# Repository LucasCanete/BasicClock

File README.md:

# BasicClock
Small atmega328p-based Clock displays the time, the temperature and humidity of the room.

## Table of Contents
1. [About the Project](#about-the-project)
2. [Project Status](#project-status)
3. [Getting Started](#getting-started)

## About the Project
Every Christmas I have to think hard what to give as a gift to my friends. As the Maker i am i decided to develop a device i could always give as a gift in Birthdays or Christmas when i dont come with any better idea. The device is a simple Clock with a big display and three buttons. The Clock lets the user see the time, temperature and humidity of the room. Additionally, the user can configure the time in case time changes or the person moves to a different timezone.

Besides from all this, i just wanted to try program different sensors with the Atmega328p using C++. I found it very convenient with the OOP so i might keep using it in the future.

Features:
- Visualization of current date, hour, temperature and humidity
- Configuration of date and hour
- USB-C port for UART communication
- Small design for being portable

## Project Status
Project is currently under development. Next Steps are the following:
- [x] Order Board from JLCPCB
- [ ] Order Stencil (i forgot it the first time)
- [ ] Solder SMD Components
- [ ] Test BME280
- [ ] Test RTC
- [ ] Test USB-C UART Communication
- [ ] Write driver for Display
- [ ] Finish writing the firmware

## Getting Started
Coming soon

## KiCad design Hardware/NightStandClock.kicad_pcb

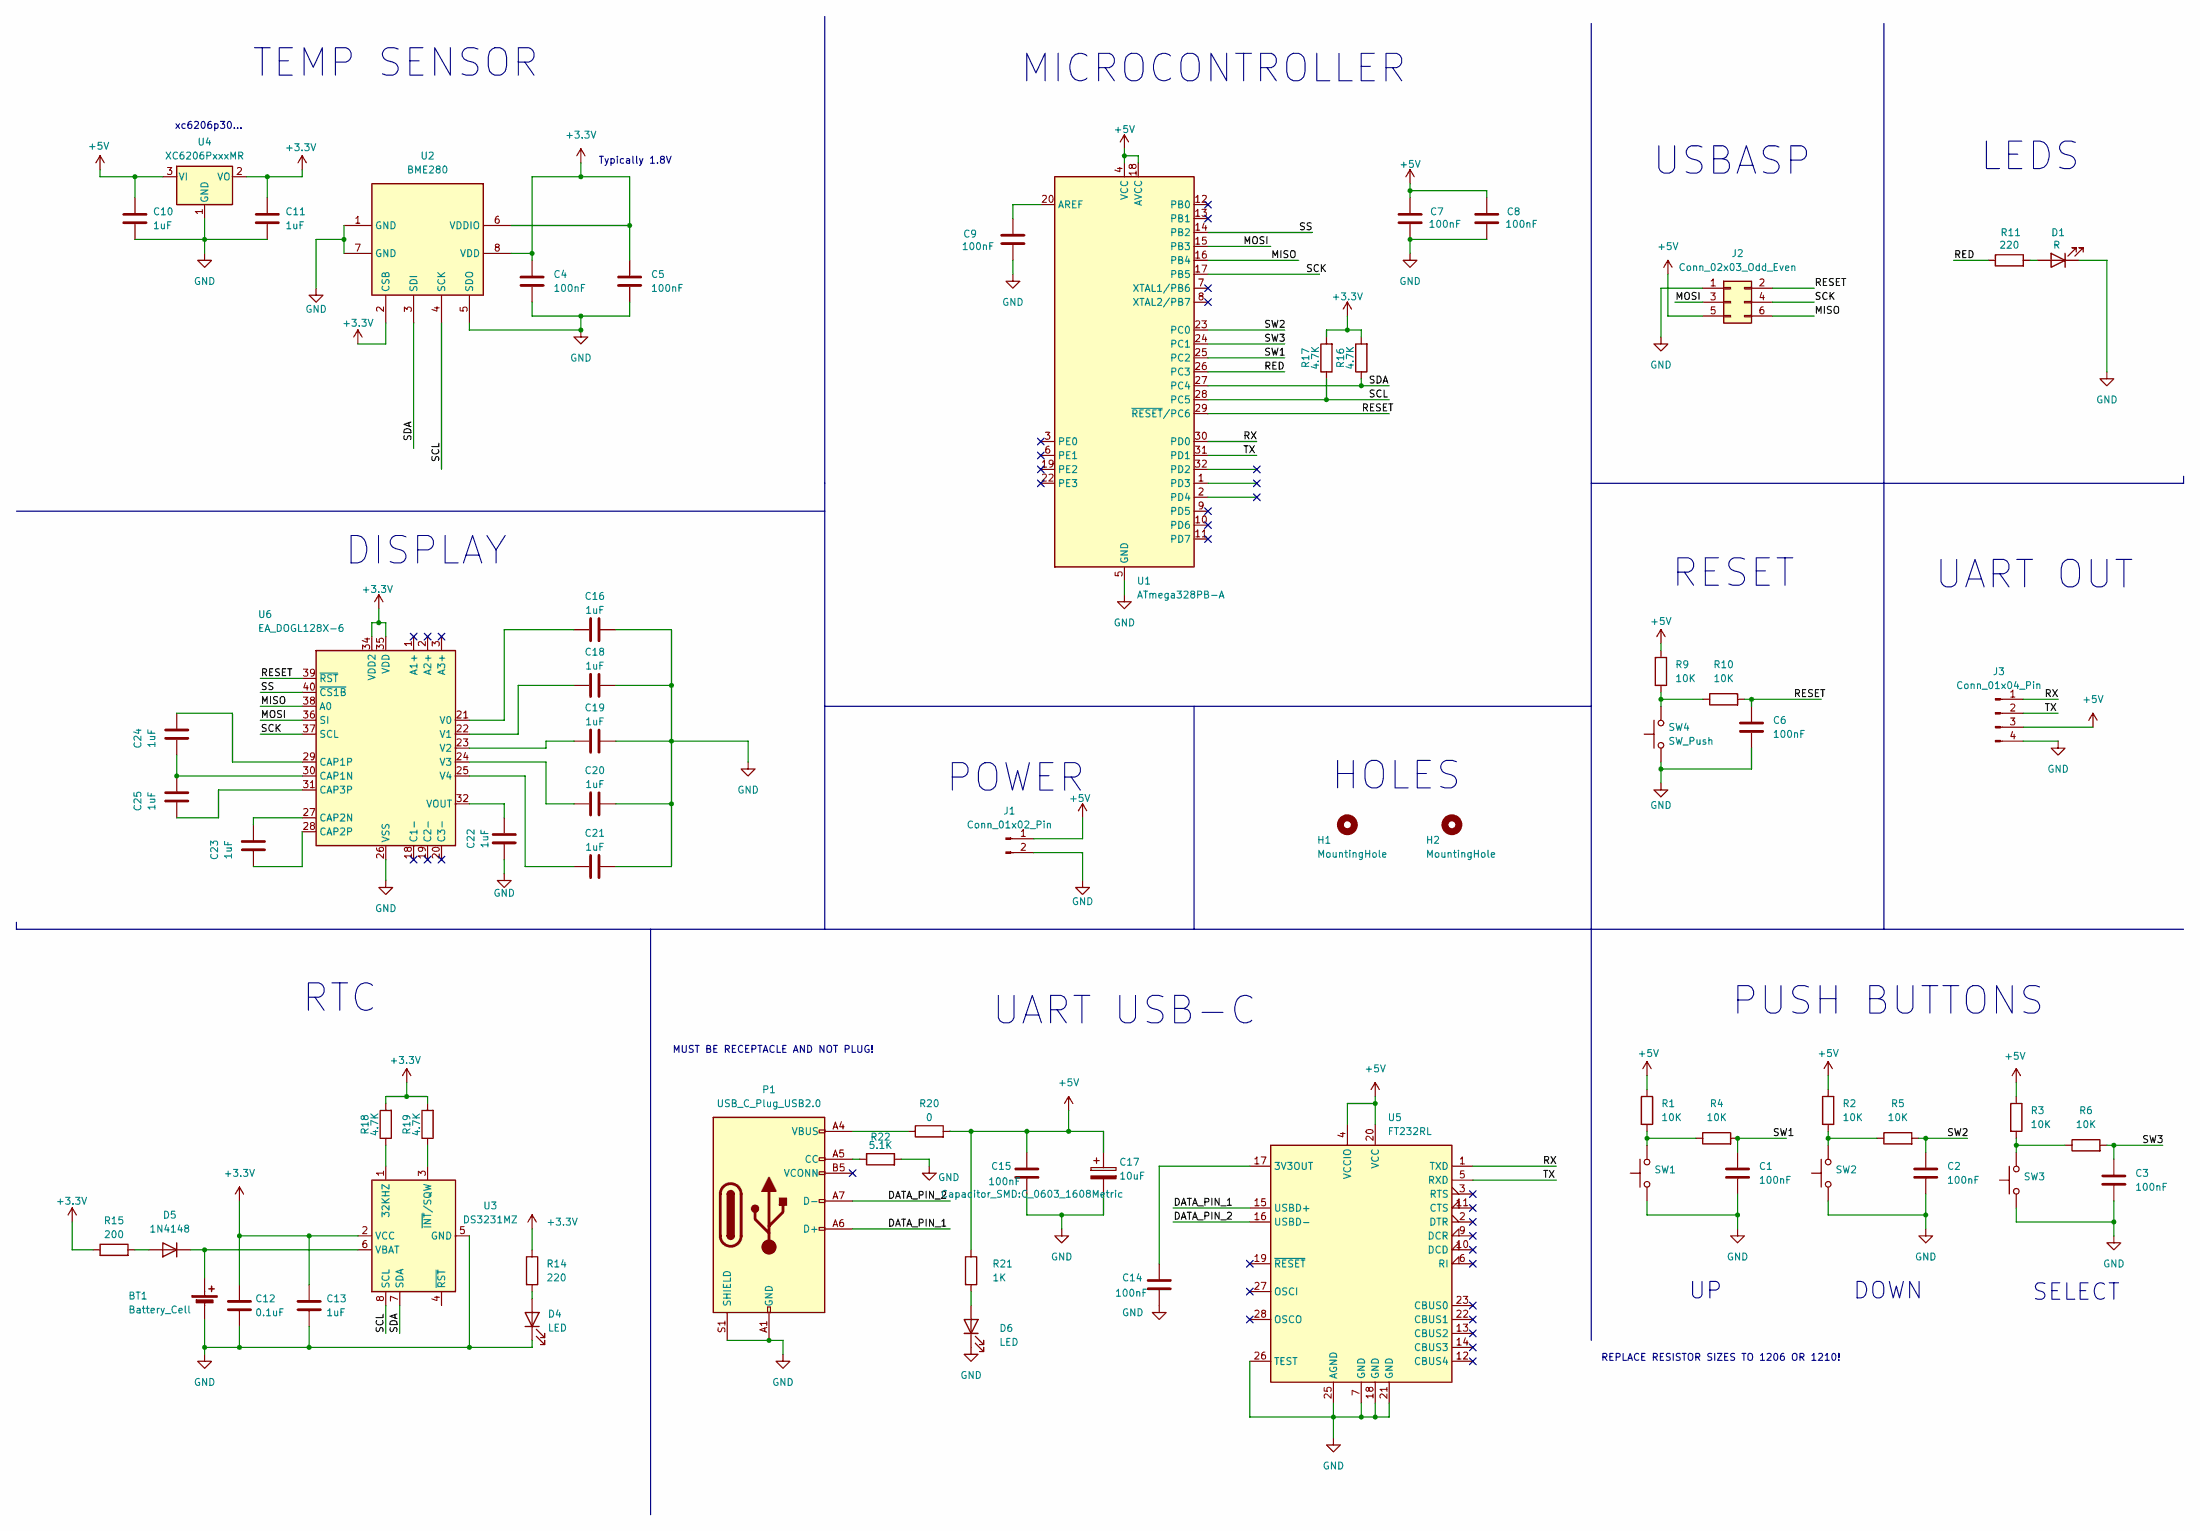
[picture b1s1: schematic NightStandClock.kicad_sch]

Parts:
BT1: Battery_Cell; BatteryHolder_MYOUNG_BS-07-A1BJ001_CR2032
C1, C2, C3, C4, C5, C6, C7, C8, C9, C14, C15: 100nF; C_0603_1608Metric
C10, C11, C13, C16, C18, C19, C20, C21, C22, C23, C24, C25: 1uF; C_0603_1608Metric
C12: 0.1uF; C_0603_1608Metric
C17: 10uF; CP_Radial_D4.0mm_P2.00mm
D1: R; LED_0603_1608Metric
D4, D6: LED; LED_0603_1608Metric
D5: 1N4148; D_0603_1608Metric
H1, H2: MountingHole; MountingHole_2.1mm
J1: Conn_01x02_Pin; JST_XH_B2B-XH-A_1x02_P2.50mm_Vertical
J2: Conn_02x03_Odd_Even; PinSocket_2x03_P2.54mm_Vertical
J3: Conn_01x04_Pin; PinHeader_1x04_P2.54mm_Vertical
P1: USB_C_Plug_USB2.0; USB_C_Receptacle_GCT_USB4105-xx-A_16P_TopMnt_Horizontal
R1, R2, R3, R4, R5, R6, R9, R10: 10K; R_0603_1608Metric
R11, R14: 220; R_0603_1608Metric
R15: 200; R_0603_1608Metric
R16, R17, R18, R19: 4.7K; R_0603_1608Metric
R20: 0; R_0603_1608Metric
R21: 1K; R_0603_1608Metric
R22: 5.1K; R_0603_1608Metric
SW1, SW2, SW3: SW_PUSH_1P1T_6x3.5mm_H4.3_APEM_MJTP1243
SW4: SW_Push; SW_PUSH_1P1T_6x3.5mm_H4.3_APEM_MJTP1243
U1: ATmega328PB-A; TQFP-32_7x7mm_P0.8mm
U2: BME280; Bosch_LGA-8_2.5x2.5mm_P0.65mm_ClockwisePinNumbering
U3: DS3231MZ; SOIC-8_3.9x4.9mm_P1.27mm
U4: XC6206PxxxMR; SOT-23
U5: FT232RL; SSOP-28_5.3x10.2mm_P0.65mm
U6: EA_DOGL128X-6; EA_DOGL128-6

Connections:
+3.3V: C4.1, C5.1, C11.1, C12.1, C13.1, R14.1, R15.1, R16.2, R17.2, R18.2, R19.2, U2.2 (CSB), U2.6 (VDDIO), U2.8 (VDD), U3.2 (VCC), U4.2 (VO), U6.34 (VDD2), U6.35 (VDD)
+5V: C7.1, C8.1, C10.1, C15.1, C17.1, J1.1, J2.5, J3.3, R1.1, R2.1, R3.1, R9.1, R20.2, R21.1, U1.4 (VCC), U1.18 (AVCC), U4.3 (VI), U5.4 (VCCIO), U5.20 (VCC)
/DATA_PIN_1: P1.A6 (D+), U5.15 (USBD+)
/DATA_PIN_2: P1.A7 (D-), U5.16 (USBD-)
/MISO: J2.6, U1.16 (PB4), U6.38 (A0)
/MOSI: J2.3, U1.15 (PB3), U6.36 (SI)
/RED: R11.1, U1.26 (PC3)
/RESET: C6.1, J2.2, R10.2, U1.29 (~RESET/PC6), U6.39 (~RST)
/RX: J3.1, U1.30 (PD0), U5.1 (TXD)
/SCK: J2.4, U1.17 (PB5), U6.37 (SCL)
/SCL: R17.1, U1.28 (PC5), U2.4 (SCK), U3.8 (SCL)
/SDA: R16.1, U1.27 (PC4), U2.3 (SDI), U3.7 (SDA)
/SS: U1.14 (PB2), U6.40 (~CS1B)
/SW1: C1.1, R4.2, U1.25 (PC2)
/SW2: C2.1, R5.2, U1.23 (PC0)
/SW3: C3.1, R6.2, U1.24 (PC1)
/TX: J3.2, U1.31 (PD1), U5.5 (RXD)
GND: BT1.2 (-), C1.2, C2.2, C3.2, C4.2, C5.2, C6.2, C7.2, C8.2, C9.2, C10.2, C11.2, C12.2, C13.2, C14.2, C15.2, C16.2, C17.2, C18.2, C19.2, C20.2, C21.2, C22.1, D1.1 (K), D4.1 (K), D6.1 (K), J1.2, J2.1, J3.4, P1.A1 (GND), P1.A12 (GND), P1.B1 (GND), P1.B12 (GND), P1.S1 (SHIELD), R22.2, SW1.1, SW2.1, SW3.1, SW4.1, U1.5 (GND), U1.21 (GND), U2.1 (GND), U2.5 (SDO), U2.7 (GND), U3.5 (GND), U4.1 (GND), U5.7 (GND), U5.18 (GND), U5.21 (GND), U5.25 (AGND), U5.26 (TEST), U6.26 (VSS), U6.33 (VSS)
unnamed: BT1.1 (+), D5.1 (K), U3.6 (VBAT)
unnamed: D1.2 (A), R11.2
unnamed: D4.2 (A), R14.2
unnamed: D5.2 (A), R15.2
unnamed: D6.2 (A), R21.2
unnamed: P1.A5 (CC), R22.1
unnamed: P1.A4 (VBUS), P1.A9 (VBUS), P1.B4 (VBUS), P1.B9 (VBUS), R20.1
unnamed: R1.2, R4.1, SW1.2
unnamed: R2.2, R5.1, SW2.2
unnamed: R3.2, R6.1, SW3.2
unnamed: R9.2, R10.1, SW4.2
unnamed: C9.1, U1.20 (AREF)
unnamed: R18.1, U3.1 (32KHZ)
unnamed: R19.1, U3.3 (~INT/SQW)
unnamed: C14.1, U5.17 (3V3OUT)
unnamed: C24.1, C25.2, U6.30 (CAP1N)
unnamed: C24.2, U6.29 (CAP1P)
unnamed: C23.2, U6.27 (CAP2N)
unnamed: C23.1, U6.28 (CAP2P)
unnamed: C25.1, U6.31 (CAP3P)
unnamed: C16.1, U6.21 (V0)
unnamed: C18.1, U6.22 (V1)
unnamed: C19.1, U6.23 (V2)
unnamed: C20.1, U6.24 (V3)
unnamed: C21.1, U6.25 (V4)
unnamed: C22.2, U6.32 (VOUT)

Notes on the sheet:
RESET
DISPLAY
REPLACE RESISTOR SIZES TO 1206 OR 1210!
Typically 1.8V
HOLES
UART USB-C
POWER
xc6206p30...
UART OUT
PUSH BUTTONS
DOWN
MUST BE RECEPTACLE AND NOT PLUG!
MICROCONTROLLER
TEMP SENSOR
SELECT
LEDS
USBASP
RTC

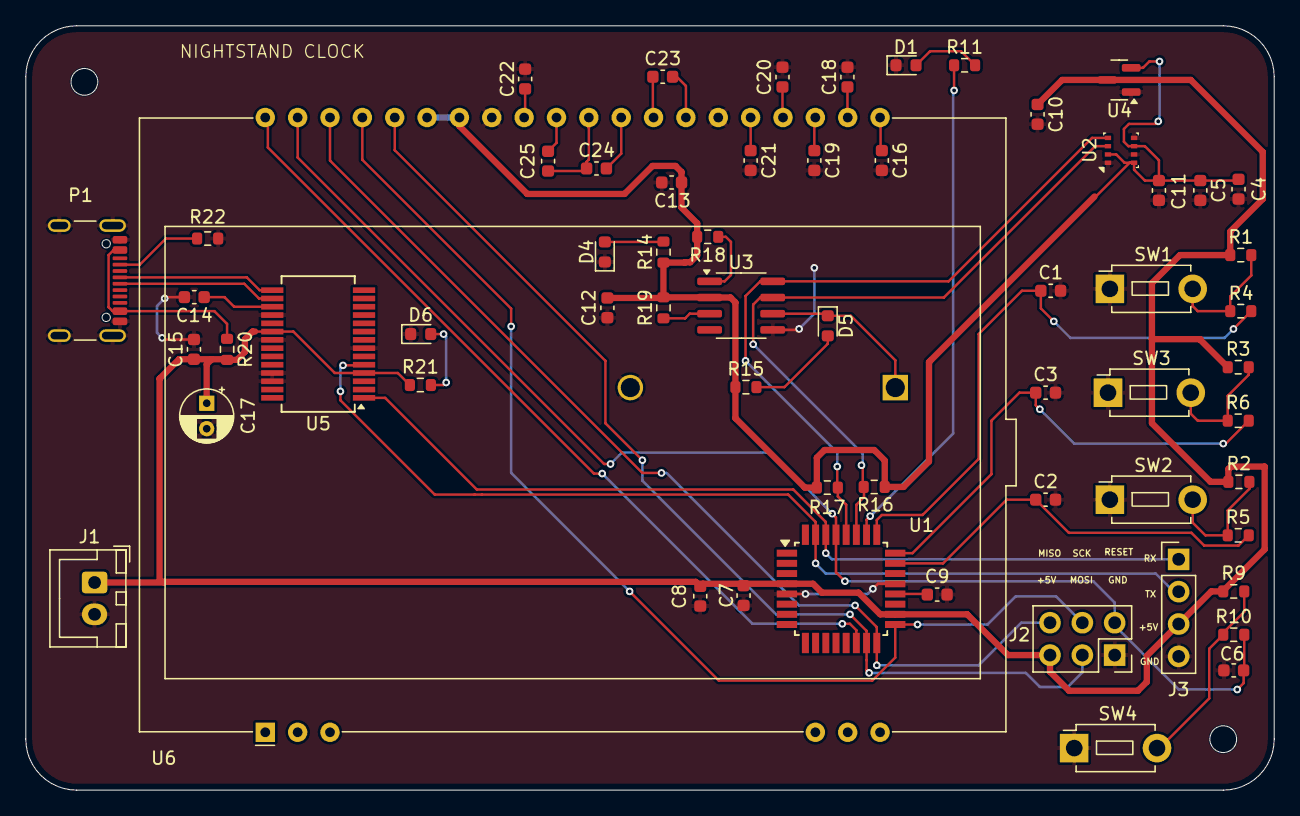
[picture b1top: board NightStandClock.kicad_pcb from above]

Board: 2 copper layers, 98.0 x 60.0 mm, 64 parts (1 on the bottom side), 44 nets.

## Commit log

2024-10-22 Added RTC
2025-02-25 added Kicad Files
2025-02-25 Rename main.cpp to Software/main.cpp
2025-02-25 Rename Makefile to Software/Makefile
